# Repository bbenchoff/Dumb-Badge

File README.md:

# VT-69 Portable Terminal

The VT-69 is a portable, battery-powered dumb terminal, along the lines of a VT-100, VT-220, Wyse WY-50, or other such microprocessor-controlled dumb terminals of the mid-80s to mid-90s. It's a portable shell, or a game console that only plays text-based adventures.

Features include:
* 4" LCD with 800x480 resolution
  * Display allows for a full 80x24 character display. *This is not a graphical display*. It will only display text characters.
  * 65536 colors, all of them.
* Silicone membrane keyboard
  * 69 keys. That's why it's the VT-69.
  * Custom-desinged, it's like the keypad on a remote control
  * Other keyboard layouts supported; DVORAK, QWERTZ, and AZERTY are simply a matter of keyboard legends.
* Battery power
  * Internal LiPo battery (> 2000 mAh) is charged from USB-C connector.
  * Provides > 12 hours of battery life.
* Microcontroller
  * ATSAMD51 clocked at blistering 120MHz
  * Custom software libraries allow for fastest text rendering possible	
* Connectivity
  * DE-9 RS-232 serial connector, provided with MAX3232
  * Serial output over USB-C connector
  * Internal UART connectors allow for internal connection to $Single Board Computer$ (a la VT-180) or any other development board with a 'standard' 40-pin header.
  * Hardware handshaking in both DE-9 RS-232 port and internal header
  * Supports _almost_ every terminal escape code recognized by the Linux console.
* Documentation
  * [Many pages of documentation](https://github.com/ViolenceWorks/VT-69/blob/main/Documentation/README.md)

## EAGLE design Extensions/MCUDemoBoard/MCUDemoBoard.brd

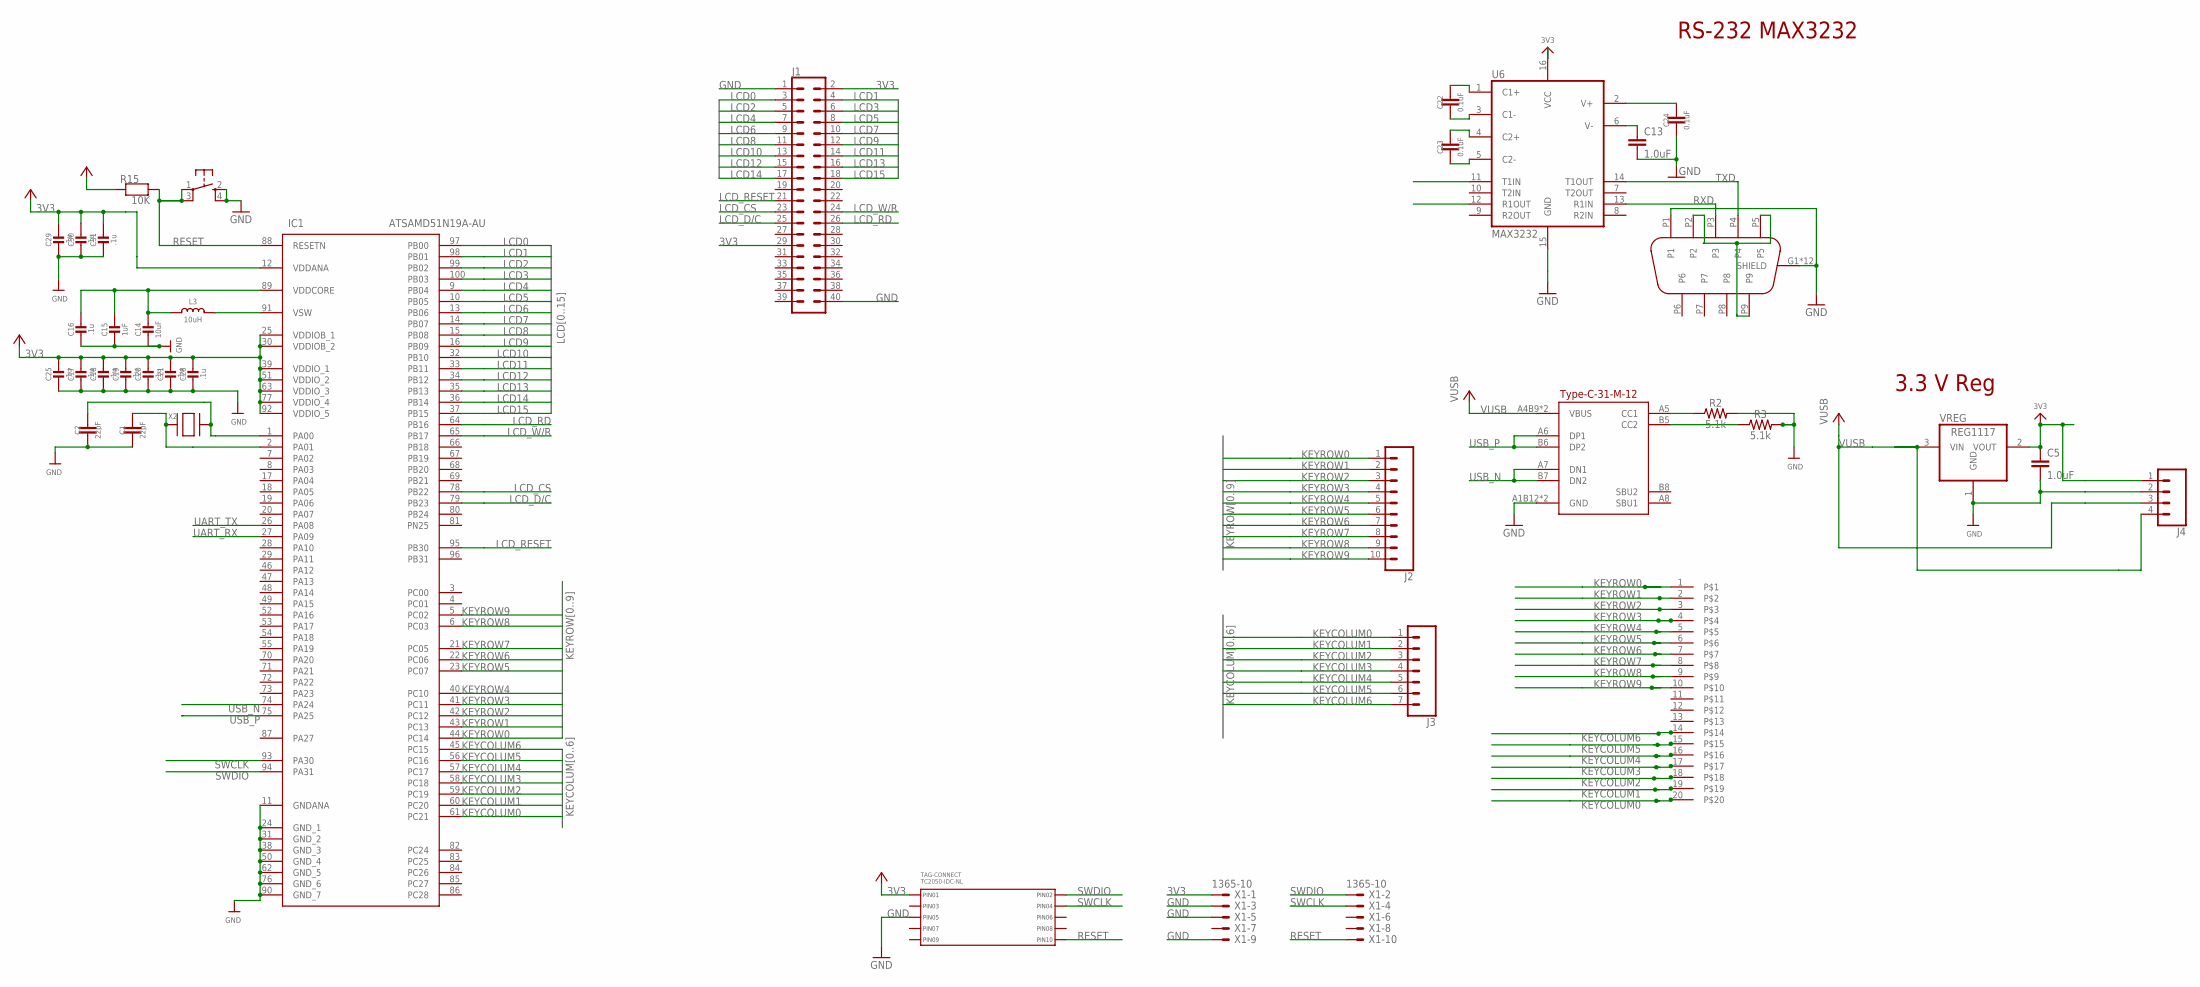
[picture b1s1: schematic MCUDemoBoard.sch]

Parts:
C1, C2: 22pF; 0805
C5, C13: 1.0uF; 0805
C14: 10uF; 0805-NO
C15: 1uF; 0603-NO
C16, C17, C18, C19, C20, C21, C25, C28, C29, C30, C31: .1u; 0603-NO
C22, C23, C24: 0.1uF; 0805
DE9FEMALE: EDGEMOUNTDE9; DE09S065TLF
IC1: ATSAMD51N19A-AU; QFP50P1600X1600X120-100N
J1: CONN_20X2NOSILK; 2X20_NOSILK
J2: CONN_10NO_SILK_PTH_FEMALE; 1X10_NO_SILK
J3: CONN_07NO_SILK; 1X07_NO_SILK
J4: CONN_04; 1X04
L3: 10uH; INDUCTOR_1007
R2, R3: 5.1k; 0603
R15: 10K; 0603-NO
SW2: SPST_TACT-KMR2; KMR2
TAG-CONNECT: TC2050-IDC-NL
U6: MAX3232; SO16
U$1: FC1-20-L2-T-WT20PIN; FC1-20-L2-T-WT
USB: TYPE-C-31-M-12
VREG: REG1117; SOT223
X1: 1365-10
X2: NX3215SA-32.768K-STD-MUA-8; XTAL3215

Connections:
3V3: C5.1, C17.2, C18.2, C19.2, C20.2, C21.2, C25.2, C28.2, C29.2, C30.2, C31.2, IC1.12 (VDDANA), IC1.25 (VDDIOB_1), IC1.30 (VDDIOB_2), IC1.39 (VDDIO_1), IC1.51 (VDDIO_2), IC1.63 (VDDIO_3), IC1.77 (VDDIO_4), IC1.92 (VDDIO_5), J1.2, J1.29, J4.1, R15.1, TAG-CONNECT.P$1 (PIN1), U6.16 (VCC), VREG.2 (VOUT), X1.1
GND: C1.1, C2.1, C5.2, C13.2, C14.2, C15.2, C16.1, C17.1, C18.1, C19.1, C20.1, C21.1, C24.2, C25.1, C28.1, C29.1, C30.1, C31.1, DE9FEMALE.G1 (SHIELD), DE9FEMALE.G2 (SHIELD), DE9FEMALE.G3 (SHIELD), DE9FEMALE.G4 (SHIELD), DE9FEMALE.G5 (SHIELD), DE9FEMALE.G6 (SHIELD), DE9FEMALE.G7 (SHIELD), DE9FEMALE.G8 (SHIELD), DE9FEMALE.G9 (SHIELD), DE9FEMALE.G10 (SHIELD), DE9FEMALE.G11 (SHIELD), DE9FEMALE.G12 (SHIELD), DE9FEMALE.P1, IC1.11 (GNDANA), IC1.24 (GND_1), IC1.31 (GND_2), IC1.38 (GND_3), IC1.50 (GND_4), IC1.62 (GND_5), IC1.76 (GND_6), IC1.90 (GND_7), J1.1, J1.40, J4.2, R2.2, R3.2, SW2.2 (S), SW2.4 (S1), TAG-CONNECT.P$5 (PIN5), U6.15 (GND), USB.A1B12 (GND), USB.B1A12 (GND), VREG.1 (GND), X1.3, X1.5, X1.9
KEYCOLUM0: IC1.61 (PC21), J3.1, U$1.20
KEYCOLUM1: IC1.60 (PC20), J3.2, U$1.19
KEYCOLUM2: IC1.59 (PC19), J3.3, U$1.18
KEYCOLUM3: IC1.58 (PC18), J3.4, U$1.17
KEYCOLUM4: IC1.57 (PC17), J3.5, U$1.16
KEYCOLUM5: IC1.56 (PC16), J3.6, U$1.15
KEYCOLUM6: IC1.45 (PC15), J3.7, U$1.14
KEYROW0: IC1.44 (PC14), J2.1, U$1.1
KEYROW1: IC1.43 (PC13), J2.2, U$1.2
KEYROW2: IC1.42 (PC12), J2.3, U$1.3
KEYROW3: IC1.41 (PC11), J2.4, U$1.4
KEYROW4: IC1.40 (PC10), J2.5, U$1.5
KEYROW5: IC1.23 (PC07), J2.6, U$1.6
KEYROW6: IC1.22 (PC06), J2.7, U$1.7
KEYROW7: IC1.21 (PC05), J2.8, U$1.8
KEYROW8: IC1.6 (PC03), J2.9, U$1.9
KEYROW9: IC1.5 (PC02), J2.10, U$1.10
LCD0: IC1.97 (PB00), J1.3
LCD1: IC1.98 (PB01), J1.4
LCD2: IC1.99 (PB02), J1.5
LCD3: IC1.100 (PB03), J1.6
LCD4: IC1.9 (PB04), J1.7
LCD5: IC1.10 (PB05), J1.8
LCD6: IC1.13 (PB06), J1.9
LCD7: IC1.14 (PB07), J1.10
LCD8: IC1.15 (PB08), J1.11
LCD9: IC1.16 (PB09), J1.12
LCD10: IC1.32 (PB10), J1.13
LCD11: IC1.33 (PB11), J1.14
LCD12: IC1.34 (PB12), J1.15
LCD13: IC1.35 (PB13), J1.16
LCD14: IC1.36 (PB14), J1.17
LCD15: IC1.37 (PB15), J1.18
LCD_CS: IC1.78 (PB22), J1.23
LCD_D/C: IC1.79 (PB23), J1.25
LCD_RD: IC1.64 (PB16), J1.26
LCD_RESET: IC1.95 (PB30), J1.21
LCD_W/R: IC1.65 (PB17), J1.24
unnamed: C24.1, U6.2 (V+)
unnamed: C2.2, IC1.1 (PA00), X2.P$1
unnamed: C1.2, IC1.2 (PA01), X2.P$2
unnamed: C22.2, U6.3 (C1-)
unnamed: C22.1, U6.1 (C1+)
unnamed: C23.1, U6.4 (C2+)
unnamed: C23.2, U6.5 (C2-)
unnamed: C13.1, U6.6 (V-)
unnamed: DE9FEMALE.P2, DE9FEMALE.P5, DE9FEMALE.P9
unnamed: R2.1, USB.A5 (CC1)
unnamed: R3.1, USB.B5 (CC2)
unnamed: C14.1, C15.1, C16.2, IC1.89 (VDDCORE), L3.P$1 (1)
unnamed: IC1.91 (VSW), L3.P$2 (2)
RESET: IC1.88 (RESETN), R15.2, SW2.1, SW2.3 (P1), TAG-CONNECT.P$10 (PIN10), X1.10
RXD: DE9FEMALE.P3, U6.13 (R1IN)
SWCLK: IC1.93 (PA30), TAG-CONNECT.P$4 (PIN4), X1.4
SWDIO: IC1.94 (PA31), TAG-CONNECT.P$2 (PIN2), X1.2
TXD: DE9FEMALE.P4, U6.14 (T1OUT)
UART_RX: IC1.27 (PA09), U6.12 (R1OUT)
UART_TX: IC1.26 (PA08), U6.11 (T1IN)
USB_N: IC1.74 (PA24), USB.A7 (DN1), USB.B7 (DN2)
USB_P: IC1.75 (PA25), USB.A6 (DP1), USB.B6 (DP2)
VUSB: J4.3, J4.4, USB.A4B9 (VBUS), USB.B4A9 (VBUS), VREG.3 (VIN)

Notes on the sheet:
RS-232 MAX3232
Type-C-31-M-12
3.3 V Reg

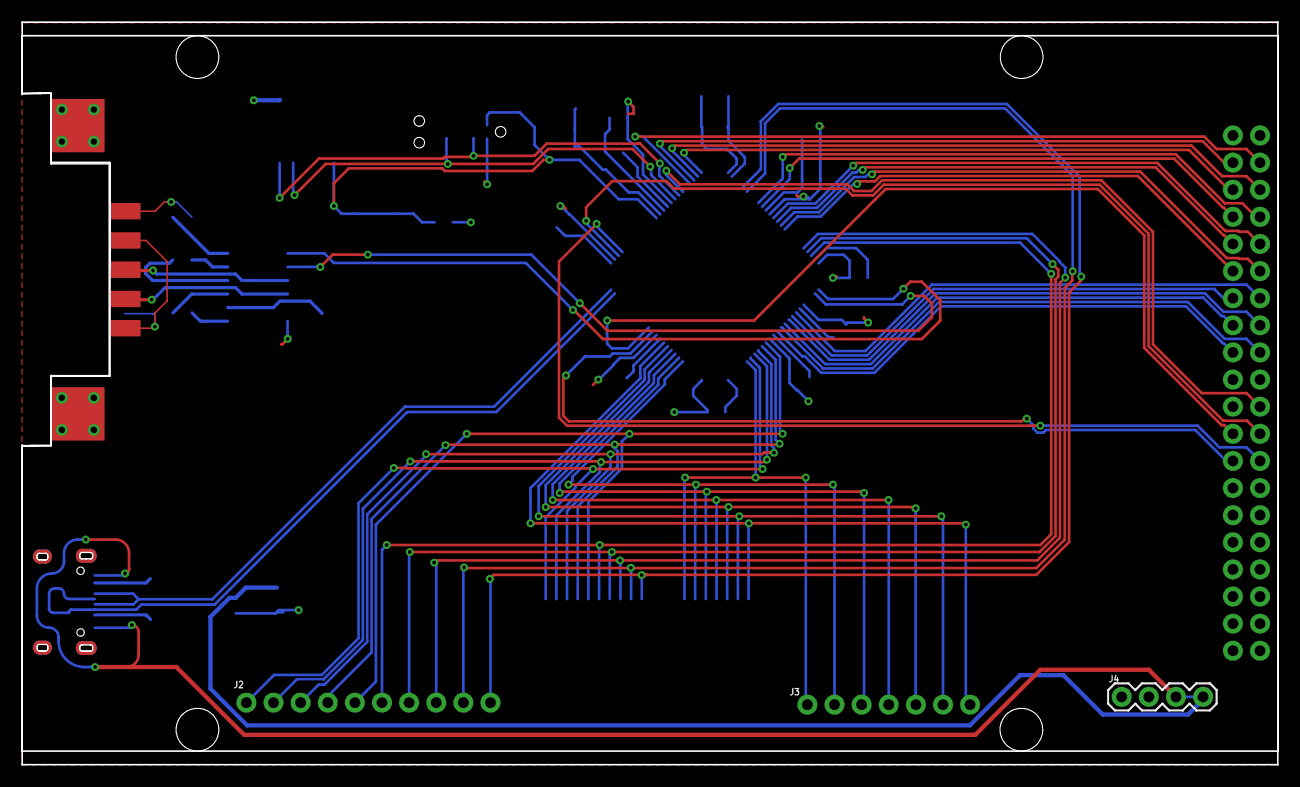
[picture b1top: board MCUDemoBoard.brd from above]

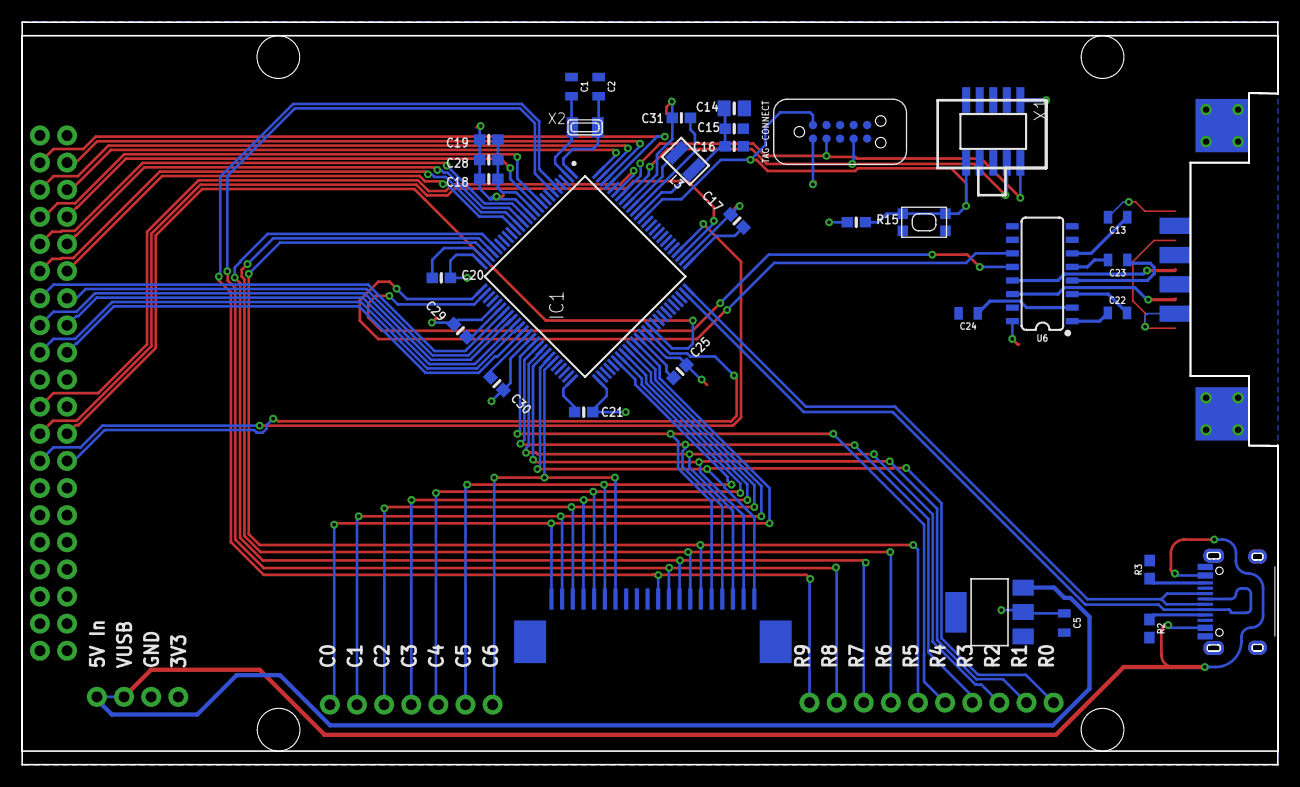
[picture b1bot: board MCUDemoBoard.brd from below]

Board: 2 copper layers, 117.6 x 69.5 mm, 38 parts (34 on the bottom side), 63 nets.

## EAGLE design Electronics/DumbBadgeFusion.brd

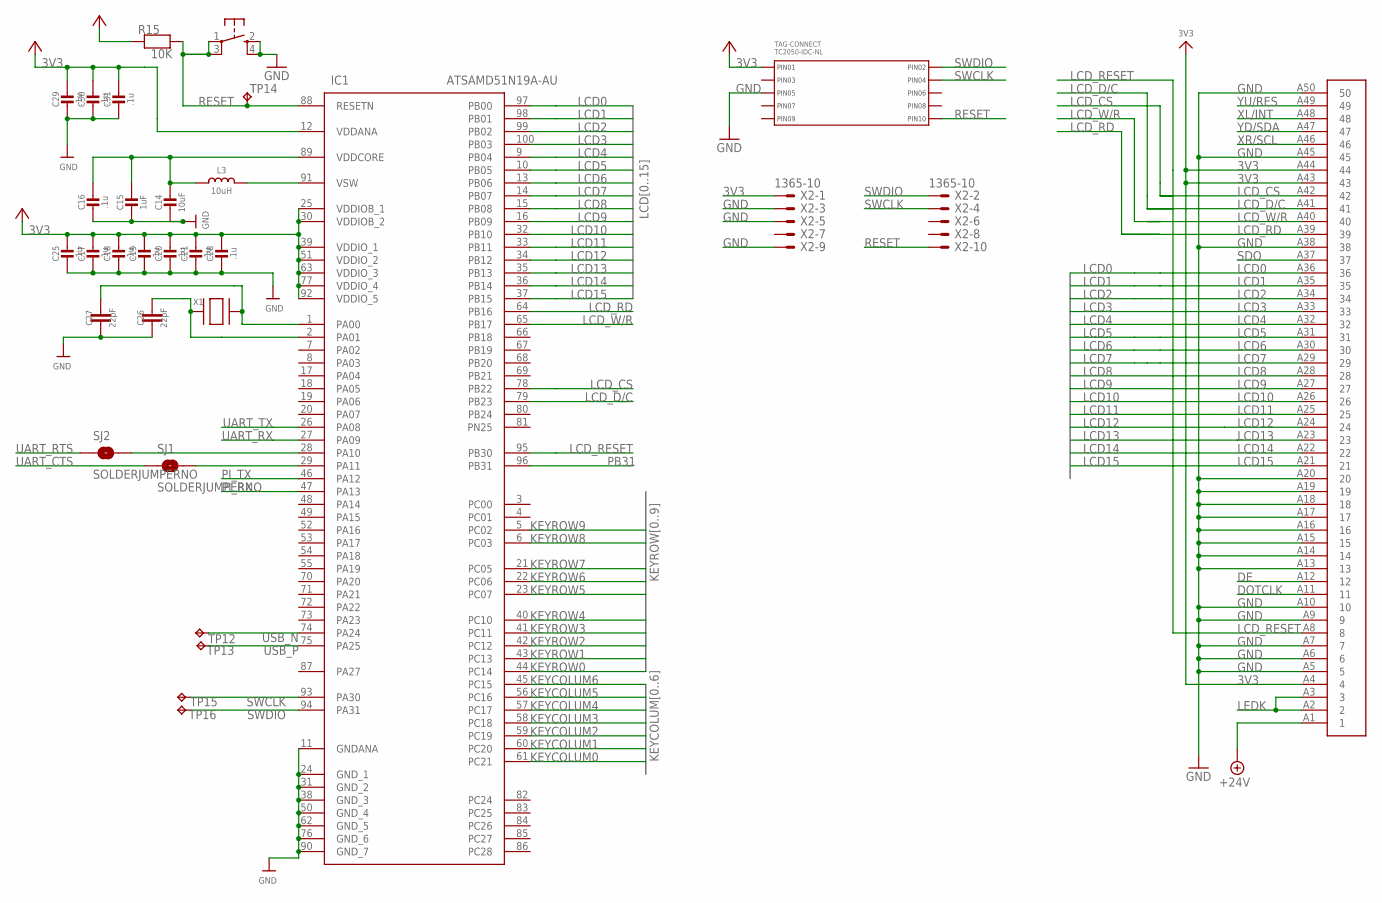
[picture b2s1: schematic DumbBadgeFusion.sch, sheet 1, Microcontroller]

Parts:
C14: 10uF; 0805-NO
C15: 1uF; 0603-NO
C16, C17, C18, C19, C20, C21, C25, C28, C29, C30, C31: .1u; 0603-NO
C26, C27: 22pF; 0805
FPC50CONN: 50PINFPC; 62684-501100ALF
IC1: ATSAMD51N19A-AU; QFP50P1600X1600X120-100N
L3: 10uH; INDUCTOR_1007
R15: 10K; 0603-NO
SJ1, SJ2: SOLDERJUMPERNO; SJ_2S-NO
SW1: SPST_TACT-KMR2; KMR2
TAG-CONNECT: TC2050-IDC-NL
TP12, TP13, TP14, TP15, TP16: TPB1,27; B1,27
X1: NX3215SA-32.768K-STD-MUA-8; XTAL3215
X2: 1365-10

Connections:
3V3: C17.2, C18.2, C19.2, C20.2, C21.2, C25.2, C28.2, C29.2, C30.2, C31.2, FPC50CONN.A4 (4), FPC50CONN.A43 (43), FPC50CONN.A44 (44), IC1.12 (VDDANA), IC1.25 (VDDIOB_1), IC1.30 (VDDIOB_2), IC1.39 (VDDIO_1), IC1.51 (VDDIO_2), IC1.63 (VDDIO_3), IC1.77 (VDDIO_4), IC1.92 (VDDIO_5), R15.1, TAG-CONNECT.P$1 (PIN1), X2.1; also elsewhere on the board
+24V: FPC50CONN.A1 (1); also elsewhere on the board
DE: FPC50CONN.A12 (12)
DOTCLK: FPC50CONN.A11 (11)
GND: C14.2, C15.2, C16.1, C17.1, C18.1, C19.1, C20.1, C21.1, C25.1, C26.1, C27.1, C28.1, C29.1, C30.1, C31.1, FPC50CONN.A5 (5), FPC50CONN.A6 (6), FPC50CONN.A7 (7), FPC50CONN.A9 (9), FPC50CONN.A10 (10), FPC50CONN.A13 (13), FPC50CONN.A14 (14), FPC50CONN.A15 (15), FPC50CONN.A16 (16), FPC50CONN.A17 (17), FPC50CONN.A18 (18), FPC50CONN.A19 (19), FPC50CONN.A20 (20), FPC50CONN.A38 (38), FPC50CONN.A45 (45), FPC50CONN.A50 (50), IC1.11 (GNDANA), IC1.24 (GND_1), IC1.31 (GND_2), IC1.38 (GND_3), IC1.50 (GND_4), IC1.62 (GND_5), IC1.76 (GND_6), IC1.90 (GND_7), SW1.2 (S), SW1.4 (S1), TAG-CONNECT.P$5 (PIN5), X2.3, X2.5, X2.9; also elsewhere on the board
KEYCOLUM0: IC1.61 (PC21); also elsewhere on the board
KEYCOLUM1: IC1.60 (PC20); also elsewhere on the board
KEYCOLUM2: IC1.59 (PC19); also elsewhere on the board
KEYCOLUM3: IC1.58 (PC18); also elsewhere on the board
KEYCOLUM4: IC1.57 (PC17); also elsewhere on the board
KEYCOLUM5: IC1.56 (PC16); also elsewhere on the board
KEYCOLUM6: IC1.45 (PC15); also elsewhere on the board
KEYROW0: IC1.44 (PC14); also elsewhere on the board
KEYROW1: IC1.43 (PC13); also elsewhere on the board
KEYROW2: IC1.42 (PC12); also elsewhere on the board
KEYROW3: IC1.41 (PC11); also elsewhere on the board
KEYROW4: IC1.40 (PC10); also elsewhere on the board
KEYROW5: IC1.23 (PC07); also elsewhere on the board
KEYROW6: IC1.22 (PC06); also elsewhere on the board
KEYROW7: IC1.21 (PC05); also elsewhere on the board
KEYROW8: IC1.6 (PC03); also elsewhere on the board
KEYROW9: IC1.5 (PC02); also elsewhere on the board
LCD0: FPC50CONN.A36 (36), IC1.97 (PB00)
LCD1: FPC50CONN.A35 (35), IC1.98 (PB01)
LCD2: FPC50CONN.A34 (34), IC1.99 (PB02)
LCD3: FPC50CONN.A33 (33), IC1.100 (PB03)
LCD4: FPC50CONN.A32 (32), IC1.9 (PB04)
LCD5: FPC50CONN.A31 (31), IC1.10 (PB05)
LCD6: FPC50CONN.A30 (30), IC1.13 (PB06)
LCD7: FPC50CONN.A29 (29), IC1.14 (PB07)
LCD8: FPC50CONN.A28 (28), IC1.15 (PB08)
LCD9: FPC50CONN.A27 (27), IC1.16 (PB09)
LCD10: FPC50CONN.A26 (26), IC1.32 (PB10)
LCD11: FPC50CONN.A25 (25), IC1.33 (PB11)
LCD12: FPC50CONN.A24 (24), IC1.34 (PB12)
LCD13: FPC50CONN.A23 (23), IC1.35 (PB13)
LCD14: FPC50CONN.A22 (22), IC1.36 (PB14)
LCD15: FPC50CONN.A21 (21), IC1.37 (PB15)
LCD_CS: FPC50CONN.A42 (42), IC1.78 (PB22)
LCD_D/C: FPC50CONN.A41 (41), IC1.79 (PB23)
LCD_RD: FPC50CONN.A39 (39), IC1.64 (PB16)
LCD_RESET: FPC50CONN.A8 (8), IC1.95 (PB30)
LCD_W/R: FPC50CONN.A40 (40), IC1.65 (PB17)
LEDK: FPC50CONN.A2 (2), FPC50CONN.A3 (3); also elsewhere on the board
unnamed: IC1.28 (PA10), SJ2.2
unnamed: C14.1, C15.1, C16.2, IC1.89 (VDDCORE), L3.P$1 (1)
unnamed: IC1.91 (VSW), L3.P$2 (2)
unnamed: IC1.29 (PA11), SJ1.2
unnamed: C27.2, IC1.1 (PA00), X1.P$1
unnamed: C26.2, IC1.2 (PA01), X1.P$2
PB31: IC1.96 (PB31); also elsewhere on the board
PI_RX: IC1.47 (PA13); also elsewhere on the board
PI_TX: IC1.46 (PA12); also elsewhere on the board
RESET: IC1.88 (RESETN), R15.2, SW1.1, SW1.3 (P1), TAG-CONNECT.P$10 (PIN10), TP14.TP, X2.10
SDO: FPC50CONN.A37 (37)
SWCLK: IC1.93 (PA30), TAG-CONNECT.P$4 (PIN4), TP15.TP, X2.4
SWDIO: IC1.94 (PA31), TAG-CONNECT.P$2 (PIN2), TP16.TP, X2.2
UART_CTS: SJ1.1; also elsewhere on the board
UART_RTS: SJ2.1; also elsewhere on the board
UART_RX: IC1.27 (PA09); also elsewhere on the board
UART_TX: IC1.26 (PA08); also elsewhere on the board
USB_N: IC1.74 (PA24), TP12.TP; also elsewhere on the board
USB_P: IC1.75 (PA25), TP13.TP; also elsewhere on the board
XL/INT: FPC50CONN.A48 (48)
XR/SCL: FPC50CONN.A46 (46)
YD/SDA: FPC50CONN.A47 (47)
YU/RES: FPC50CONN.A49 (49)

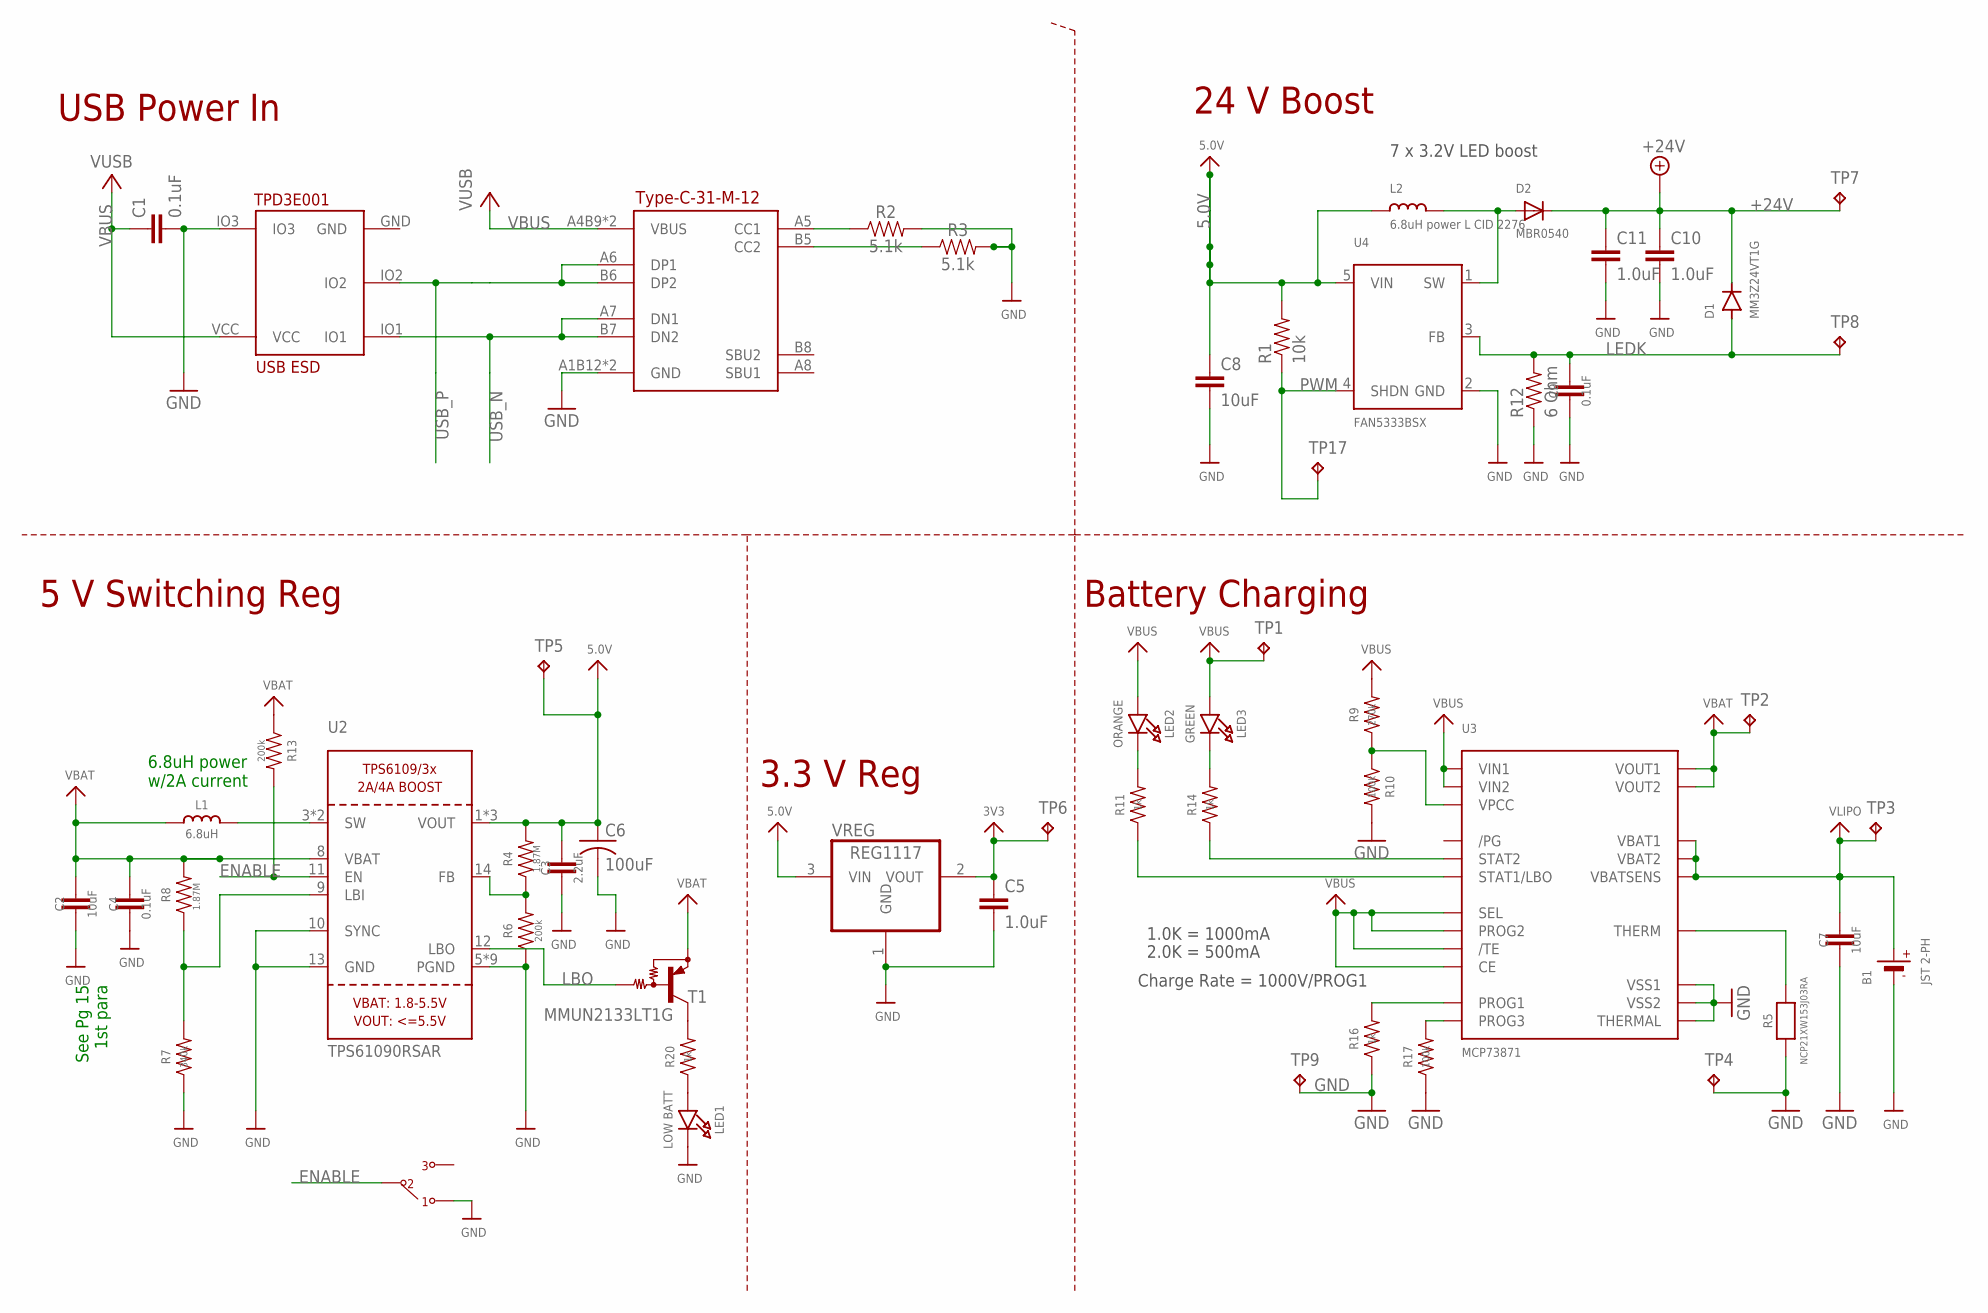
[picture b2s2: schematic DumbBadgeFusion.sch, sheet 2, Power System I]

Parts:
B1: JST 2-PH; JSTPH2
C1, C4, C9: 0.1uF; 0805
C2, C7, C8: 10uF; 0805
C3: 2.2uF; 0805
C5, C10, C11: 1.0uF; 0805
C6: 100uF; C1210
D1: MM3Z24VT1G; SOD323-W
D2: MBR0540; SOD-123
L1: 6.8uH; INDUCTOR_5X5MM_TDK_VLC5045
L2: 6.8uH power L CID 2276; INDUCTOR_5X5MM_NR5040_NOTHERMALS
LED1: LOW BATT; CHIPLED_0805_NOOUTLINE
LED2: ORANGE; CHIPLED_0805_NOOUTLINE
LED3: GREEN; CHIPLED_0805_NOOUTLINE
R1: 10k; 0603
R2, R3: 5.1k; 0603
R4, R8: 1.87M; 0603
R5: NCP21XW153J03RA; 0805-NO
R6, R13: 200k; 0603
R7: 340k; 0603
R9: 270k; 0603
R10, R17: 100k; 0603
R11, R14, R16, R20: 1k; 0603
R12: 6 Ohm; 0603
T1: MMUN2133LT1G; SC59-BEC
TP1, TP2, TP3, TP4, TP5, TP6, TP7, TP8, TP9, TP17: TPB1,27; B1,27
U2: TPS61090RSAR; PVQFN-16
U3: MCP73871; QFN20_4MM
U4: FAN5333BSX; SOT23-5@1
U5: TPD3E001SOT5; SOT(5)
U$5: OS102011MA1QN1
USB: TYPE-C-31-M-12
VREG: REG1117; SOT223

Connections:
3V3: C5.1, TP6.TP, VREG.2 (VOUT); also elsewhere on the board
5.0V: C3.1, C6.1, C8.1, L2.P$1 (1), R1.2, R4.2, TP5.TP, U2.1 (VOUT), U2.15 (VOUT), U2.16 (VOUT), U4.5 (VIN), VREG.3 (VIN); also elsewhere on the board
+24V: C10.1, C11.1, D1.C, D2.C, TP7.TP; also elsewhere on the board
ENABLE: R13.2, U2.11 (EN), U$5.P$2
GND: B1.1 (-), C1.2, C2.2, C3.2, C4.2, C5.2, C6.2, C7.2, C8.2, C9.2, C10.2, C11.2, LED1.C, R2.2, R3.2, R5.1, R6.1, R7.1, R10.2, R12.1, R16.1, R17.1, TP4.TP, TP9.TP, U2.5 (PGND), U2.6 (PGND), U2.7 (PGND), U2.10 (SYNC), U2.13 (GND), U2.P$18 (PGND), U2.P$19 (PGND), U2.P$20 (PGND), U2.P$21 (PGND), U2.P$22 (PGND), U2.THERMAL (PGND), U3.P$10 (VSS1), U3.P$11 (VSS2), U3.P$21 (THERMAL), U4.2 (GND), U5.IO3, U$5.P$1, USB.A1B12 (GND), USB.B1A12 (GND), VREG.1 (GND); also elsewhere on the board
LBO: T1.B, U2.12 (LBO)
LEDK: C9.1, D1.A, R12.2, TP8.TP, U4.3 (FB); also elsewhere on the board
unnamed: L1.P$2 (2), U2.3 (SW), U2.4 (SW)
unnamed: R7.2, R8.1, U2.9 (LBI)
unnamed: LED1.A, R20.1
unnamed: R4.1, R6.2, U2.14 (FB)
unnamed: R20.2, T1.C
unnamed: R9.1, R10.1, U3.P$2 (VPCC)
unnamed: R14.1, U3.P$7 (STAT2)
unnamed: R11.1, U3.P$8 (STAT1/LBO)
unnamed: R5.2, U3.P$5 (THERM)
unnamed: R16.2, U3.P$13 (PROG1)
unnamed: LED3.C, R14.2
unnamed: LED2.C, R11.2
unnamed: R17.2, U3.P$12 (PROG3)
unnamed: D2.A, L2.P$2 (2), U4.1 (SW)
unnamed: R2.1, USB.A5 (CC1)
unnamed: R3.1, USB.B5 (CC2)
PWM: R1.1, TP17.TP, U4.4 (SHDN)
USB_N: U5.IO1, USB.A7 (DN1), USB.B7 (DN2); also elsewhere on the board
USB_P: U5.IO2, USB.A6 (DP1), USB.B6 (DP2); also elsewhere on the board
VBAT: C2.1, C4.1, L1.P$1 (1), R8.2, R13.1, T1.E, TP2.TP, U2.8 (VBAT), U3.P$1 (VOUT1), U3.P$20 (VOUT2)
VBUS: C1.1, LED2.A, LED3.A, R9.2, TP1.TP, U3.P$3 (SEL), U3.P$4 (PROG2), U3.P$9 (/TE), U3.P$17 (CE), U3.P$18 (VIN1), U3.P$19 (VIN2), U5.VCC, USB.A4B9 (VBUS), USB.B4A9 (VBUS)
VLIPO: B1.2 (+), C7.1, TP3.TP, U3.P$14 (VBAT1), U3.P$15 (VBAT2), U3.P$16 (VBATSENS)

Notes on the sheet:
Type-C-31-M-12
USB Power In
See Pg 15 1st para
6.8uH power w/2A current
Charge Rate = 1000V/PROG1
1.0K = 1000mA
2.0K = 500mA
3.3 V Reg
Battery Charging
5 V Switching Reg
7 x 3.2V LED boost
24 V Boost

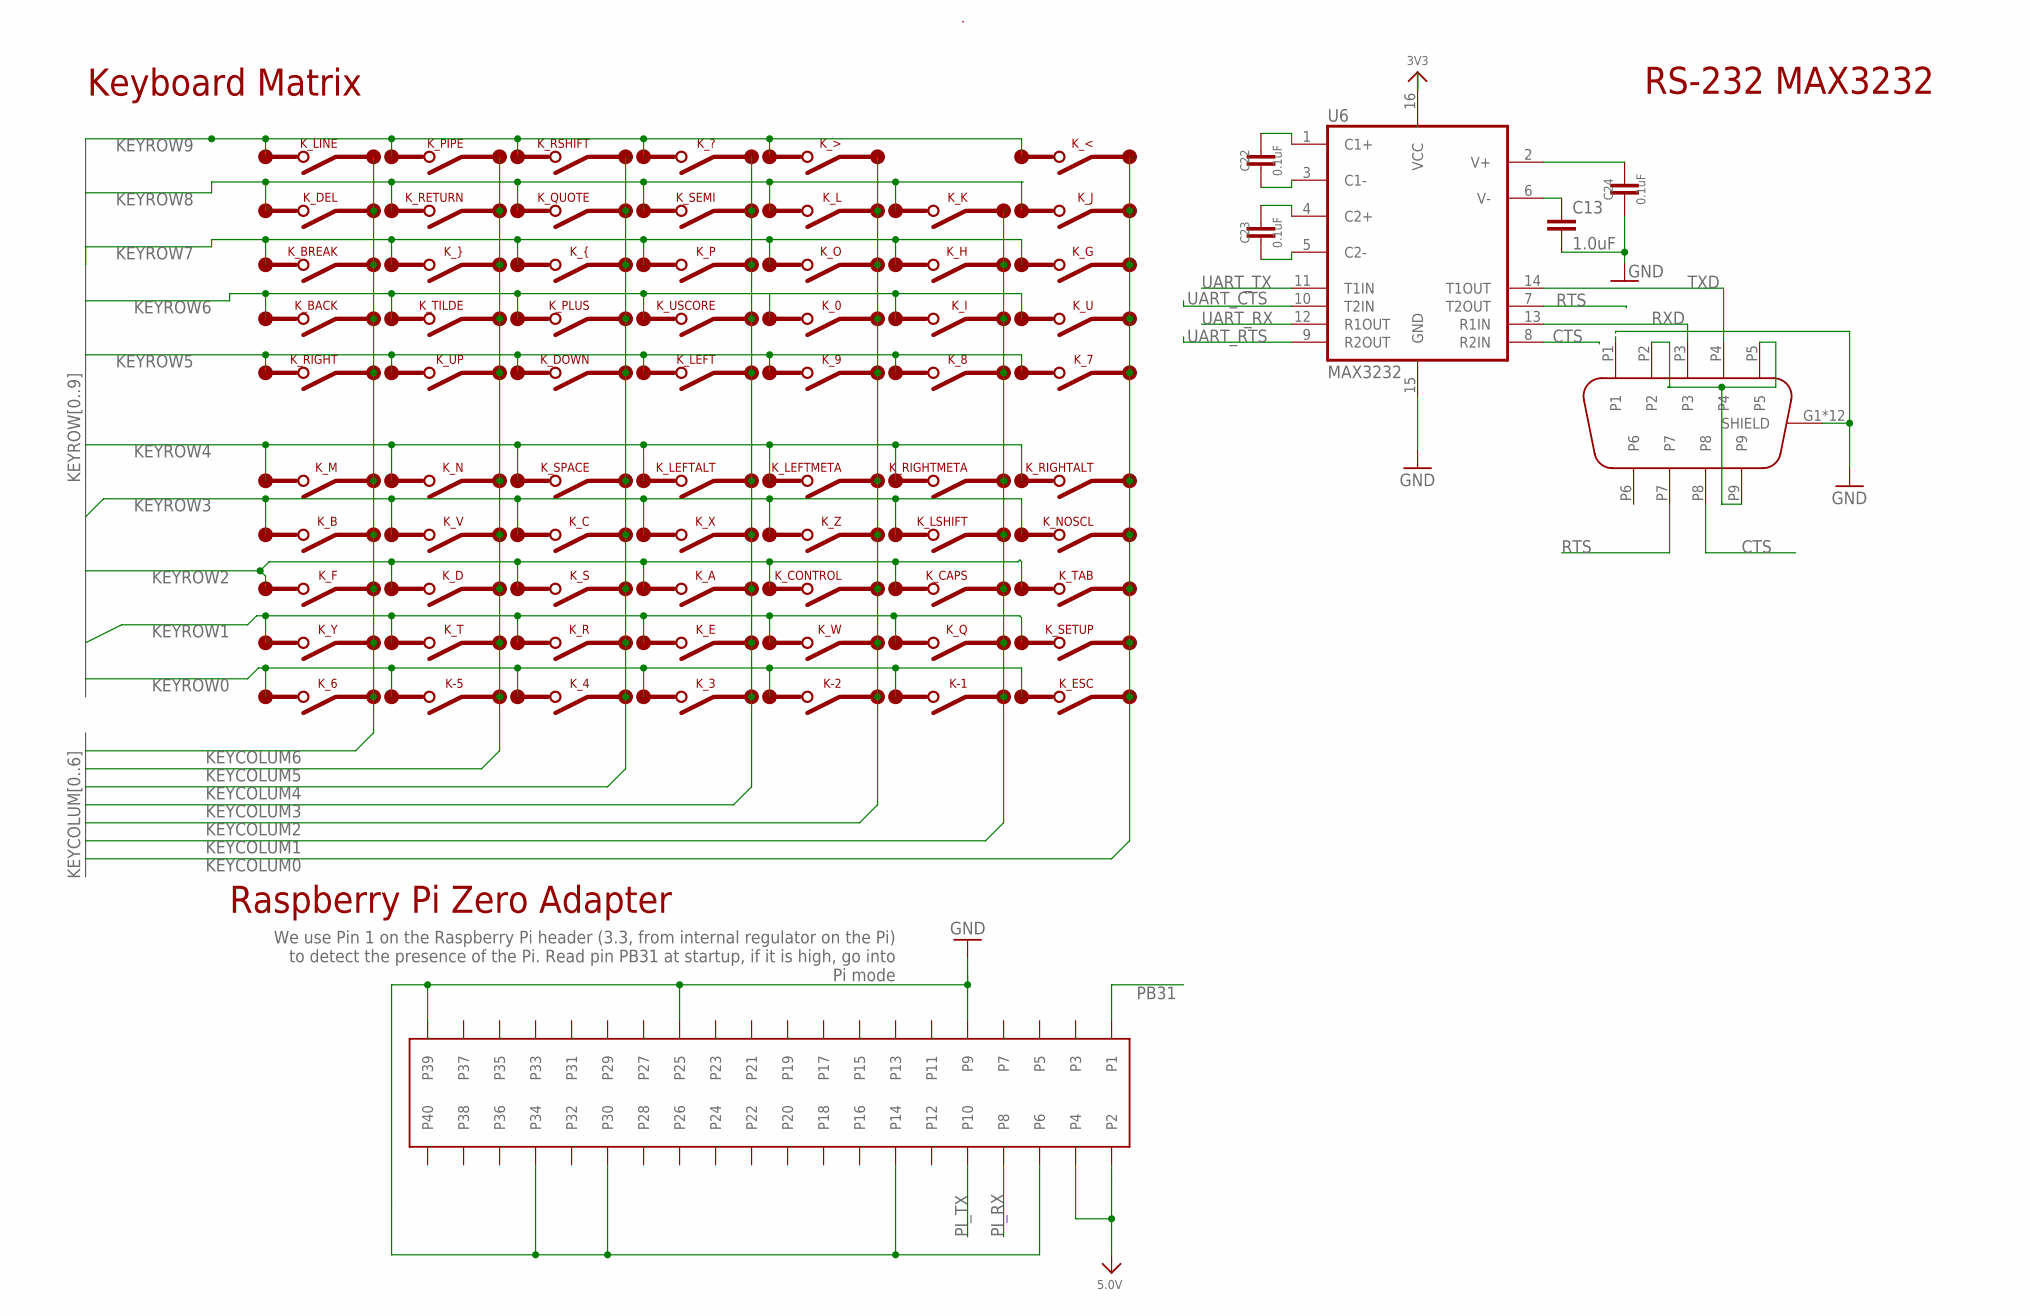
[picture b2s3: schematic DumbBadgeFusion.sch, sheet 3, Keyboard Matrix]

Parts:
C13: 1.0uF; 0805
C22, C23, C24: 0.1uF; 0805
DE9FEMALE: EDGEMOUNTDE9; DE09S065TLF
K-1, K-2, K-5: 1U_PAD; SILICONE_SWITCH
K_0, K_3, K_4, K_6, K_7, K_8, K_9: 1U_PAD; SILICONE_SWITCH
K_<: 1U_PAD; SILICONE_SWITCH
K_>: 1U_PAD; SILICONE_SWITCH
K_?: 1U_PAD; SILICONE_SWITCH
K_A: 1U_PAD; SILICONE_SWITCH
K_B: 1U_PAD; SILICONE_SWITCH
K_BACK: 1U_PAD; SILICONE_SWITCH
K_BREAK: 1U_PAD; SILICONE_SWITCH
K_C: 1U_PAD; SILICONE_SWITCH
K_CAPS: 1U_PAD; SILICONE_SWITCH
K_CONTROL: 2U_PAD; SILICONE_SWITCH_2U
K_D: 1U_PAD; SILICONE_SWITCH
K_DEL: 1U_PAD; SILICONE_SWITCH
K_DOWN: 1U_PAD; SILICONE_SWITCH
K_E: 1U_PAD; SILICONE_SWITCH
K_ESC: 1U_PAD; SILICONE_SWITCH
K_F: 1U_PAD; SILICONE_SWITCH
K_G: 1U_PAD; SILICONE_SWITCH
K_H: 1U_PAD; SILICONE_SWITCH
K_I: 1U_PAD; SILICONE_SWITCH
K_J: 1U_PAD; SILICONE_SWITCH
K_K: 1U_PAD; SILICONE_SWITCH
K_L: 1U_PAD; SILICONE_SWITCH
K_LEFT: 1U_PAD; SILICONE_SWITCH
K_LEFTALT: 1U_PAD; SILICONE_SWITCH
K_LEFTMETA: 1U_PAD; SILICONE_SWITCH
K_LINE: 1U_PAD; SILICONE_SWITCH
K_LSHIFT: 2U_PAD; SILICONE_SWITCH_2U
K_M: 1U_PAD; SILICONE_SWITCH
K_N: 1U_PAD; SILICONE_SWITCH
K_NOSCL: 1U_PAD; SILICONE_SWITCH
K_O: 1U_PAD; SILICONE_SWITCH
K_P: 1U_PAD; SILICONE_SWITCH
K_PIPE: 1U_PAD; SILICONE_SWITCH
K_PLUS: 1U_PAD; SILICONE_SWITCH
K_Q: 1U_PAD; SILICONE_SWITCH
K_QUOTE: 1U_PAD; SILICONE_SWITCH
K_R: 1U_PAD; SILICONE_SWITCH
K_RETURN: RETURN_PAD; SILICONE_RETURN
K_RIGHT: 1U_PAD; SILICONE_SWITCH
K_RIGHTALT: 1U_PAD; SILICONE_SWITCH
K_RIGHTMETA: 1U_PAD; SILICONE_SWITCH
K_RSHIFT: 2U_PAD; SILICONE_SWITCH_2U
K_S: 1U_PAD; SILICONE_SWITCH
K_SEMI: 1U_PAD; SILICONE_SWITCH
K_SETUP: 2U_PAD; SILICONE_SWITCH_2U
K_SPACE: SPACE_PAD; SILICONE_SPACE
K_T: 1U_PAD; SILICONE_SWITCH
K_TAB: 1U_PAD; SILICONE_SWITCH
K_TILDE: 1U_PAD; SILICONE_SWITCH
K_U: 1U_PAD; SILICONE_SWITCH
K_UP: 1U_PAD; SILICONE_SWITCH
K_USCORE: 1U_PAD; SILICONE_SWITCH
K_V: 1U_PAD; SILICONE_SWITCH
K_W: 1U_PAD; SILICONE_SWITCH
K_X: 1U_PAD; SILICONE_SWITCH
K_Y: 1U_PAD; SILICONE_SWITCH
K_Z: 1U_PAD; SILICONE_SWITCH
K_{: 1U_PAD; SILICONE_SWITCH
K_}: 1U_PAD; SILICONE_SWITCH
U6: MAX3232; SO16
U$30: SAMTEC_PI_REVERSE; HLE-120-02-G-DV-BE-A--REVERSEMOUNT

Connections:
3V3: U6.16 (VCC); also elsewhere on the board
5.0V: U$30.P2, U$30.P4; also elsewhere on the board
CTS: DE9FEMALE.P8, U6.8 (R2IN)
GND: C13.2, C24.2, DE9FEMALE.G1 (SHIELD), DE9FEMALE.G2 (SHIELD), DE9FEMALE.G3 (SHIELD), DE9FEMALE.G4 (SHIELD), DE9FEMALE.G5 (SHIELD), DE9FEMALE.G6 (SHIELD), DE9FEMALE.G7 (SHIELD), DE9FEMALE.G8 (SHIELD), DE9FEMALE.G9 (SHIELD), DE9FEMALE.G10 (SHIELD), DE9FEMALE.G11 (SHIELD), DE9FEMALE.G12 (SHIELD), DE9FEMALE.P1, U6.15 (GND), U$30.P6, U$30.P9, U$30.P14, U$30.P25, U$30.P30, U$30.P34, U$30.P39; also elsewhere on the board
KEYCOLUM0: K_7.P$2, K_<.P$2, K_ESC.P$2, K_G.P$2, K_J.P$2, K_NOSCL.P$2, K_RIGHTALT.P$2, K_SETUP.P$2, K_TAB.P$2, K_U.P$2; also elsewhere on the board
KEYCOLUM1: K-1.P$2, K_8.P$2, K_CAPS.P$2, K_H.P$2, K_I.P$2, K_K.P$2, K_LSHIFT.P$2, K_Q.P$2, K_RIGHTMETA.P$2; also elsewhere on the board
KEYCOLUM2: K-2.P$2, K_0.P$2, K_9.P$2, K_>.P$2, K_CONTROL.P$2, K_L.P$2, K_LEFTMETA.P$2, K_O.P$2, K_W.P$2, K_Z.P$2; also elsewhere on the board
KEYCOLUM3: K_3.P$2, K_?.P$2, K_A.P$2, K_E.P$2, K_LEFT.P$2, K_LEFTALT.P$2, K_P.P$2, K_SEMI.P$2, K_USCORE.P$2, K_X.P$2; also elsewhere on the board
KEYCOLUM4: K_4.P$2, K_C.P$2, K_DOWN.P$2, K_PLUS.P$2, K_QUOTE.P$2, K_R.P$2, K_RSHIFT.P$2, K_S.P$2, K_SPACE.P$2, K_{.P$2; also elsewhere on the board
KEYCOLUM5: K-5.P$2, K_D.P$2, K_N.P$2, K_PIPE.P$2, K_RETURN.P$2, K_T.P$2, K_TILDE.P$2, K_UP.P$2, K_V.P$2, K_}.P$2; also elsewhere on the board
KEYCOLUM6: K_6.P$2, K_B.P$2, K_BACK.P$2, K_BREAK.P$2, K_DEL.P$2, K_F.P$2, K_LINE.P$2, K_M.P$2, K_RIGHT.P$2, K_Y.P$2; also elsewhere on the board
KEYROW0: K-1.P$1, K-2.P$1, K-5.P$1, K_3.P$1, K_4.P$1, K_6.P$1, K_ESC.P$1; also elsewhere on the board
KEYROW1: K_E.P$1, K_Q.P$1, K_R.P$1, K_SETUP.P$1, K_T.P$1, K_W.P$1, K_Y.P$1; also elsewhere on the board
KEYROW2: K_A.P$1, K_CAPS.P$1, K_CONTROL.P$1, K_D.P$1, K_F.P$1, K_S.P$1, K_TAB.P$1; also elsewhere on the board
KEYROW3: K_B.P$1, K_C.P$1, K_LSHIFT.P$1, K_NOSCL.P$1, K_V.P$1, K_X.P$1, K_Z.P$1; also elsewhere on the board
KEYROW4: K_LEFTALT.P$1, K_LEFTMETA.P$1, K_M.P$1, K_N.P$1, K_RIGHTALT.P$1, K_RIGHTMETA.P$1, K_SPACE.P$1; also elsewhere on the board
KEYROW5: K_7.P$1, K_8.P$1, K_9.P$1, K_DOWN.P$1, K_LEFT.P$1, K_RIGHT.P$1, K_UP.P$1; also elsewhere on the board
KEYROW6: K_0.P$1, K_BACK.P$1, K_I.P$1, K_PLUS.P$1, K_TILDE.P$1, K_U.P$1, K_USCORE.P$1; also elsewhere on the board
KEYROW7: K_BREAK.P$1, K_G.P$1, K_H.P$1, K_O.P$1, K_P.P$1, K_{.P$1, K_}.P$1; also elsewhere on the board
KEYROW8: K_DEL.P$1, K_J.P$1, K_K.P$1, K_L.P$1, K_QUOTE.P$1, K_RETURN.P$1, K_SEMI.P$1; also elsewhere on the board
KEYROW9: K_<.P$1, K_>.P$1, K_?.P$1, K_LINE.P$1, K_PIPE.P$1, K_RSHIFT.P$1; also elsewhere on the board
unnamed: C24.1, U6.2 (V+)
unnamed: C22.2, U6.3 (C1-)
unnamed: C22.1, U6.1 (C1+)
unnamed: C23.1, U6.4 (C2+)
unnamed: C23.2, U6.5 (C2-)
unnamed: C13.1, U6.6 (V-)
unnamed: DE9FEMALE.P2, DE9FEMALE.P5, DE9FEMALE.P9
PB31: U$30.P1; also elsewhere on the board
PI_RX: U$30.P8; also elsewhere on the board
PI_TX: U$30.P10; also elsewhere on the board
RTS: DE9FEMALE.P7, U6.7 (T2OUT)
RXD: DE9FEMALE.P3, U6.13 (R1IN)
TXD: DE9FEMALE.P4, U6.14 (T1OUT)
UART_CTS: U6.10 (T2IN); also elsewhere on the board
UART_RTS: U6.9 (R2OUT); also elsewhere on the board
UART_RX: U6.12 (R1OUT); also elsewhere on the board
UART_TX: U6.11 (T1IN); also elsewhere on the board

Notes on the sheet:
Keyboard Matrix
RS-232 MAX3232
Raspberry Pi Zero Adapter
We use Pin 1 on the Raspberry Pi header (3.3, from internal regulator on the Pi) to detect the presence of the Pi. Read pin PB31 at startup, if it is high, go into Pi mode

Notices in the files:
parts and their libraries:
microbuilder: This work is placed in the public domain, and may be freely used for commercial and non-commercial work with the following conditions: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
SparkFun-IC-Comms: Licensing: Creative Commons ShareAlike 4.0 International - https://creativecommons.org/licenses/by-sa/4.0
